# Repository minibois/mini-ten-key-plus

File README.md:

# mini-ten-key-plus
## Repository for the mini Ten Key Plus, a Pro Micro based numpad/macropad PCB, suitable for up to 25 MX(-like) keyswitches and a (tactile) rotary encoder.
It is recommended to download the latest release of this project: https://github.com/minibois/ten-key-plus/releases

 This PCB can be used using a 3D printed plate and case, also provided in this repository

 _Render of the front and back of the PCB respectively_

 << [License](https://github.com/minibois/ten-key-plus/tree/master/LICENSE) || [Assembly Guide](https://github.com/minibois/ten-key-plus/blob/master/Documents/Assembly%20Guide.pdf) || BOM ([Octoparts](https://octopart.com/bom-tool/pvFPXgm8)) / ([.txt](https://github.com/minibois/ten-key-plus/blob/master/Documents/BOM.txt)) / ([.xlsx](https://github.com/minibois/ten-key-plus/blob/master/Documents/BOM.xlsx)) || [Supported layouts](https://raw.githubusercontent.com/minibois/ten-key-plus/master/Documents/Layouts/layouts.png) || Schematic ([.pdf](https://github.com/minibois/ten-key-plus/blob/master/Documents/Schematic.pdf)) / ([.sch](https://github.com/minibois/ten-key-plus/blob/master/mini-ten-key-plus.sch)) || PCB ([.pdf](https://github.com/minibois/ten-key-plus/blob/master/Documents/PCB.pdf)) / ([.kicad_pcb](https://github.com/minibois/ten-key-plus/blob/master/mini-ten-key-plus.kicad_pcb)) >>

 The PCB and schematic are licensed under CERN-OHL-S v2, full license details can be found here: https://github.com/minibois/ten-key-plus/tree/master/LICENSE/LICENSE.txt.

## Libraries used in this project (most of them adapted to this project):
 * That-Canadian's KiCad_labs (for the D-SOD123_axial-dual): https://github.com/That-Canadian/KiCad_Libs
 * Type-C.Pretty: https://github.com/ai03-2725/Type-C.pretty
 * MX_Alps_Hybrid: https://github.com/ai03-2725/MX_Alps_Hybrid
 * random-keyboard-parts (for a reset switch): https://github.com/ai03-2725/random-keyboard-parts.pretty

### This PCB file and schematic is provided - as per CERN-OHL-S v2 section 6 - _without any warranty_ (implied or otherwise). https://ohwr.org/cern_ohl_s_v2.pdf
### The assembly guide is provided under the CC BY-SA 4.0, without any warranty (implied or otherwise): https://creativecommons.org/licenses/by-sa/4.0/legalcode

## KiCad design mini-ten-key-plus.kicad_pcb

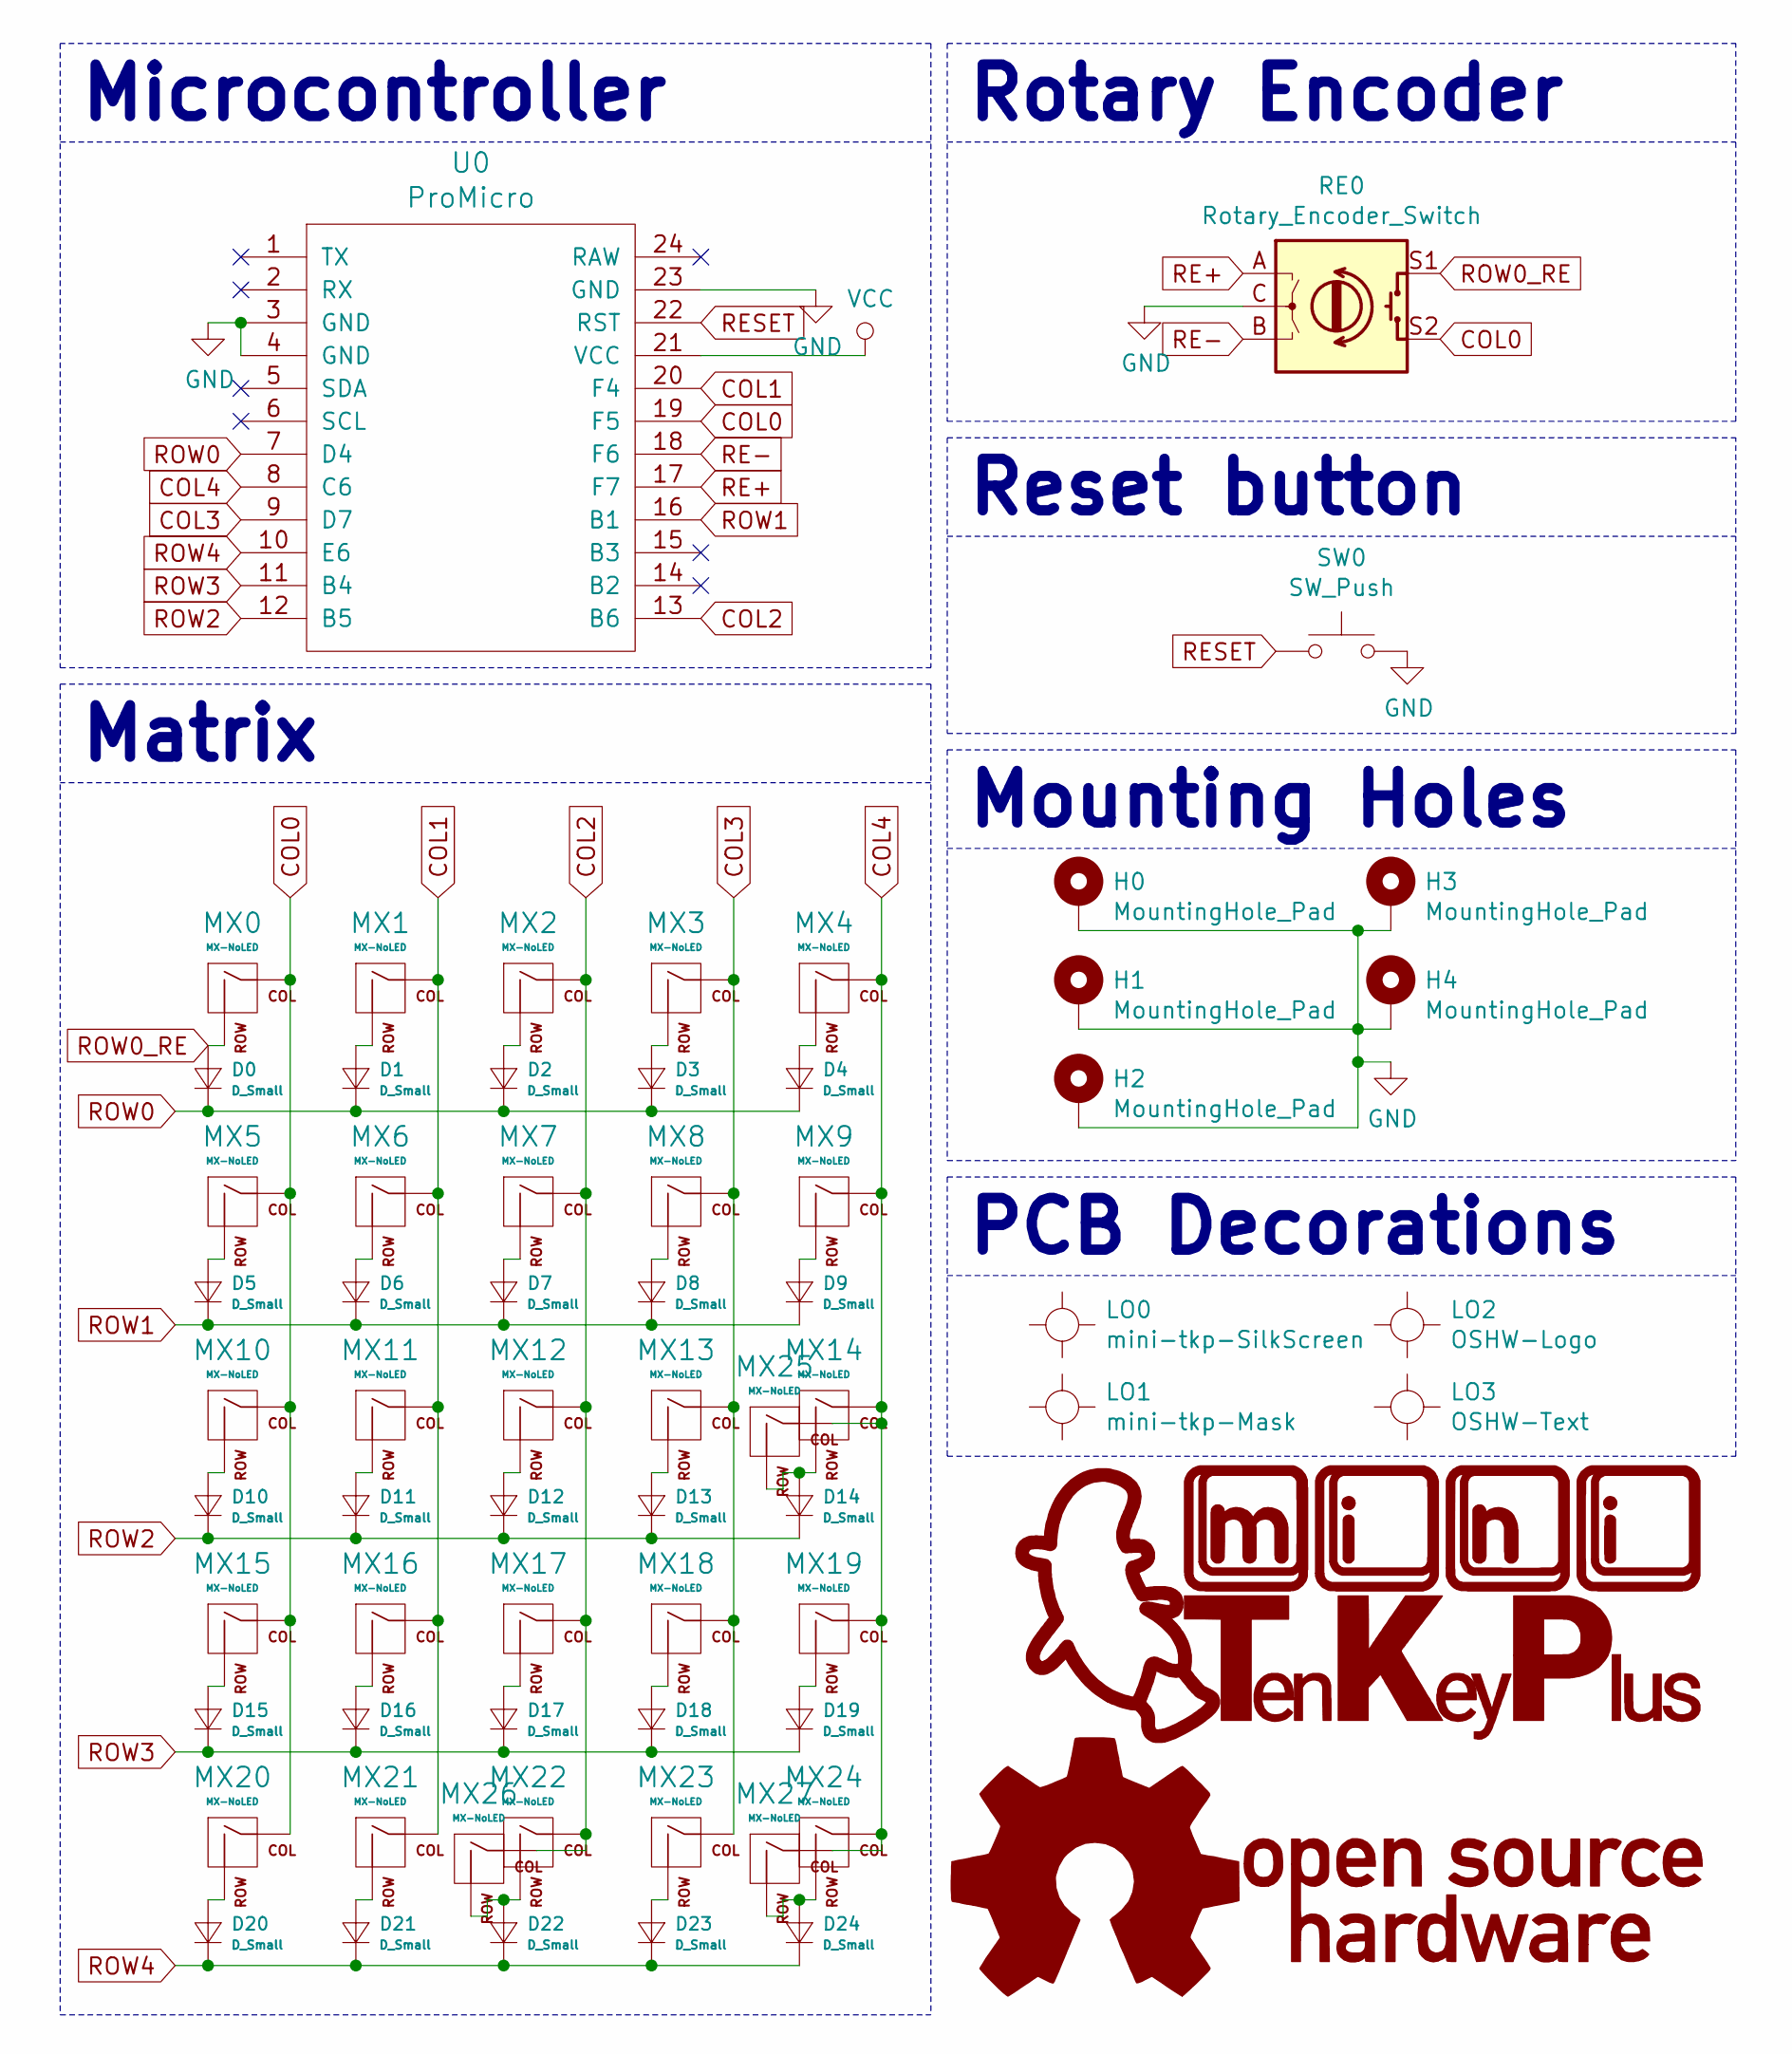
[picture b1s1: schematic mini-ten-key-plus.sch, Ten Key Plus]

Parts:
D0, D1, D2, D3, D4, D5, D6, D7, D8, D9, D10, D11, D12, D13, D14, D15, D16, D17, D18, D19, D20, D21, D22, D23, D24: D_Small; D_SOD123_axial-dual
H0, H1, H2, H3, H4: MountingHole_Pad; MountingHole_2.2mm_M2_Pad_tweaked
LO0: mini-tkp-SilkScreen; mini-TKP-BSilk
LO1: mini-tkp-Mask; mini-TKP-BMask
LO2: OSHW-Logo
LO3: OSHW-Text
MX0, MX1, MX2, MX3, MX4, MX5, MX6, MX7, MX8, MX9, MX10, MX11, MX12, MX13, MX14, MX15, MX16, MX17, MX18, MX19, MX20, MX21, MX22, MX23, MX24: MX-NoLED; MXOnly-1U-NoLED_tweak
MX25, MX27: MX-NoLED; MXOnly-2U-NoLED_tweak
MX26: MX-NoLED; MXOnly-2U-NoLED_FLIPPED_tweak
RE0: Rotary_Encoder_Switch; RotaryEncoder_Alps_EC11E-Switch-Vertical-EDIT
SW0: SW_Push; SKQG-1155865
U0: ProMicro

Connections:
COL0: MX0.1 (COL), MX5.1 (COL), MX10.1 (COL), MX15.1 (COL), MX20.1 (COL), RE0.S2, U0.19 (F5)
COL1: MX1.1 (COL), MX6.1 (COL), MX11.1 (COL), MX16.1 (COL), MX21.1 (COL), U0.20 (F4)
COL2: MX2.1 (COL), MX7.1 (COL), MX12.1 (COL), MX17.1 (COL), MX22.1 (COL), MX26.1 (COL), U0.13 (B6)
COL3: MX3.1 (COL), MX8.1 (COL), MX13.1 (COL), MX18.1 (COL), MX23.1 (COL), U0.9 (D7)
COL4: MX4.1 (COL), MX9.1 (COL), MX14.1 (COL), MX19.1 (COL), MX24.1 (COL), MX25.1 (COL), MX27.1 (COL), U0.8 (C6)
GND: H0.1, H1.1, H2.1, H3.1, H4.1, RE0.C, SW0.2, U0.3 (GND), U0.4 (GND), U0.23 (GND); also elsewhere on the board
unnamed: D1.2 (A), MX1.2 (ROW)
unnamed: D2.2 (A), MX2.2 (ROW)
unnamed: D3.2 (A), MX3.2 (ROW)
unnamed: D4.2 (A), MX4.2 (ROW)
unnamed: D5.2 (A), MX5.2 (ROW)
unnamed: D6.2 (A), MX6.2 (ROW)
unnamed: D7.2 (A), MX7.2 (ROW)
unnamed: D8.2 (A), MX8.2 (ROW)
unnamed: D9.2 (A), MX9.2 (ROW)
unnamed: D10.2 (A), MX10.2 (ROW)
unnamed: D11.2 (A), MX11.2 (ROW)
unnamed: D12.2 (A), MX12.2 (ROW)
unnamed: D13.2 (A), MX13.2 (ROW)
unnamed: D14.2 (A), MX14.2 (ROW), MX25.2 (ROW)
unnamed: D15.2 (A), MX15.2 (ROW)
unnamed: D16.2 (A), MX16.2 (ROW)
unnamed: D17.2 (A), MX17.2 (ROW)
unnamed: D18.2 (A), MX18.2 (ROW)
unnamed: D19.2 (A), MX19.2 (ROW)
unnamed: D20.2 (A), MX20.2 (ROW)
unnamed: D21.2 (A), MX21.2 (ROW)
unnamed: D22.2 (A), MX22.2 (ROW), MX26.2 (ROW)
unnamed: D23.2 (A), MX23.2 (ROW)
unnamed: D24.2 (A), MX24.2 (ROW), MX27.2 (ROW)
RE+: RE0.A, U0.17 (F7)
RE-: RE0.B, U0.18 (F6)
RESET: SW0.1, U0.22 (RST); also elsewhere on the board
ROW0: D0.1 (K), D1.1 (K), D2.1 (K), D3.1 (K), D4.1 (K), U0.7 (D4)
ROW0_RE: D0.2 (A), MX0.2 (ROW), RE0.S1
ROW1: D5.1 (K), D6.1 (K), D7.1 (K), D8.1 (K), D9.1 (K), U0.16 (B1)
ROW2: D10.1 (K), D11.1 (K), D12.1 (K), D13.1 (K), D14.1 (K), U0.12 (B5)
ROW3: D15.1 (K), D16.1 (K), D17.1 (K), D18.1 (K), D19.1 (K), U0.11 (B4)
ROW4: D20.1 (K), D21.1 (K), D22.1 (K), D23.1 (K), D24.1 (K), U0.10 (E6)
VCC: U0.21 (VCC)

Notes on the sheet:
Matrix
Microcontroller
Reset button
Mounting Holes
PCB Decorations
Rotary Encoder

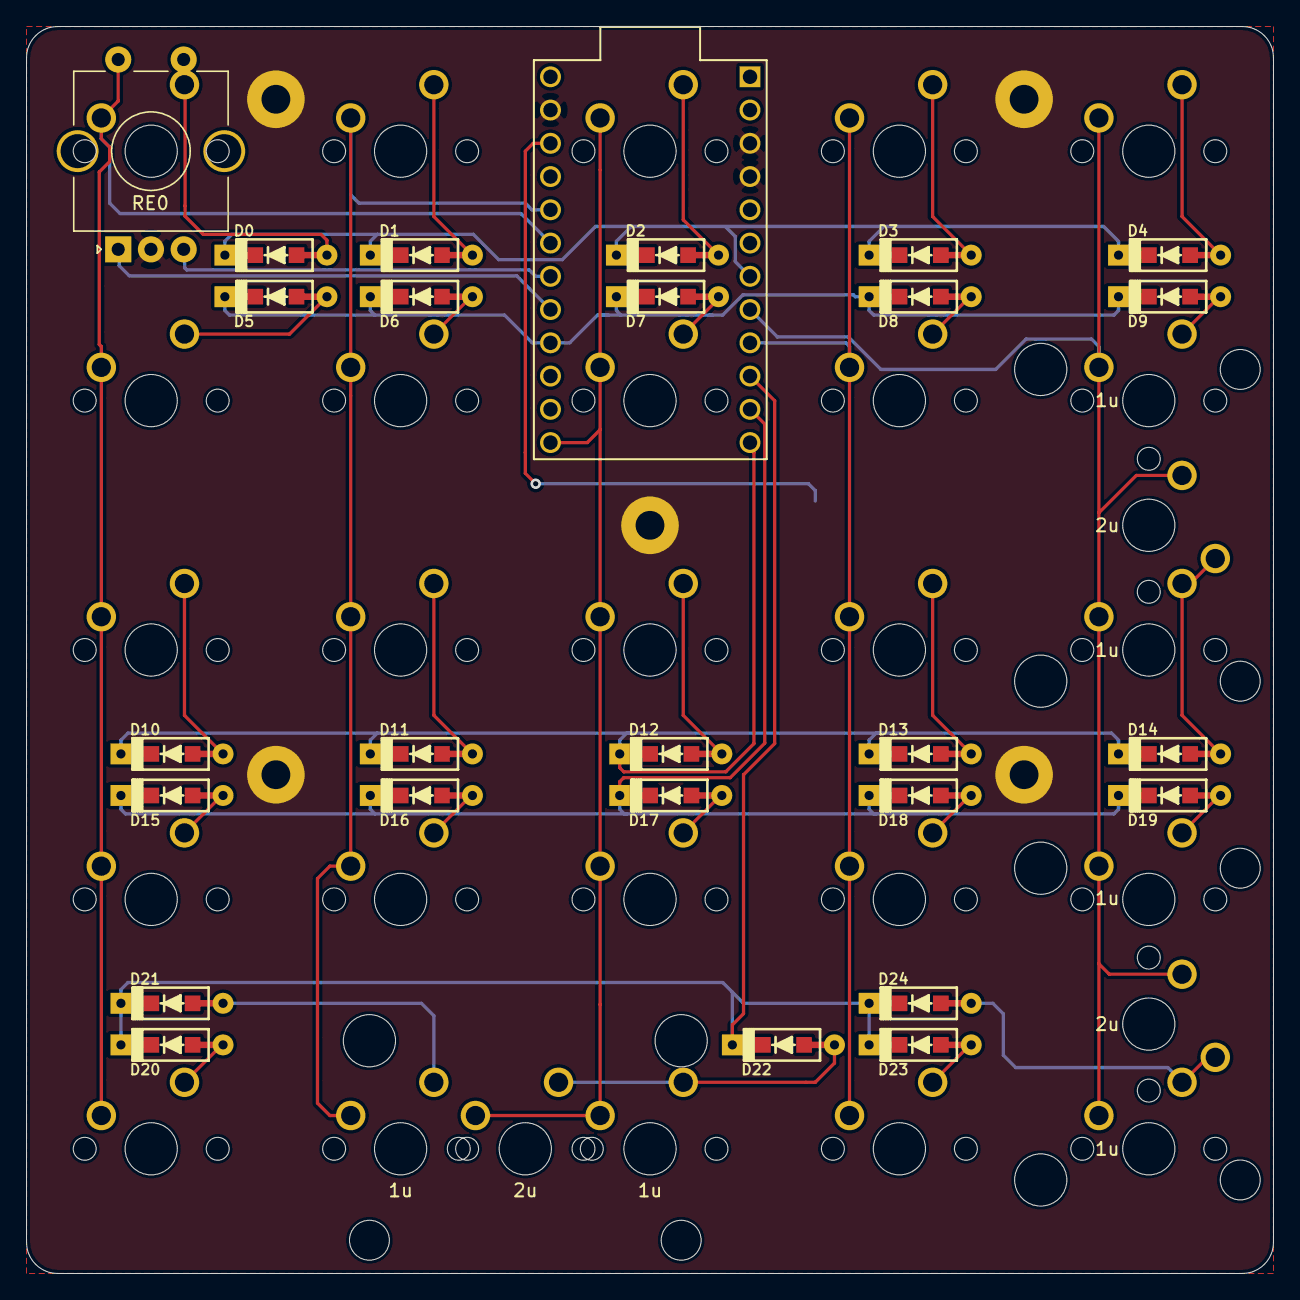
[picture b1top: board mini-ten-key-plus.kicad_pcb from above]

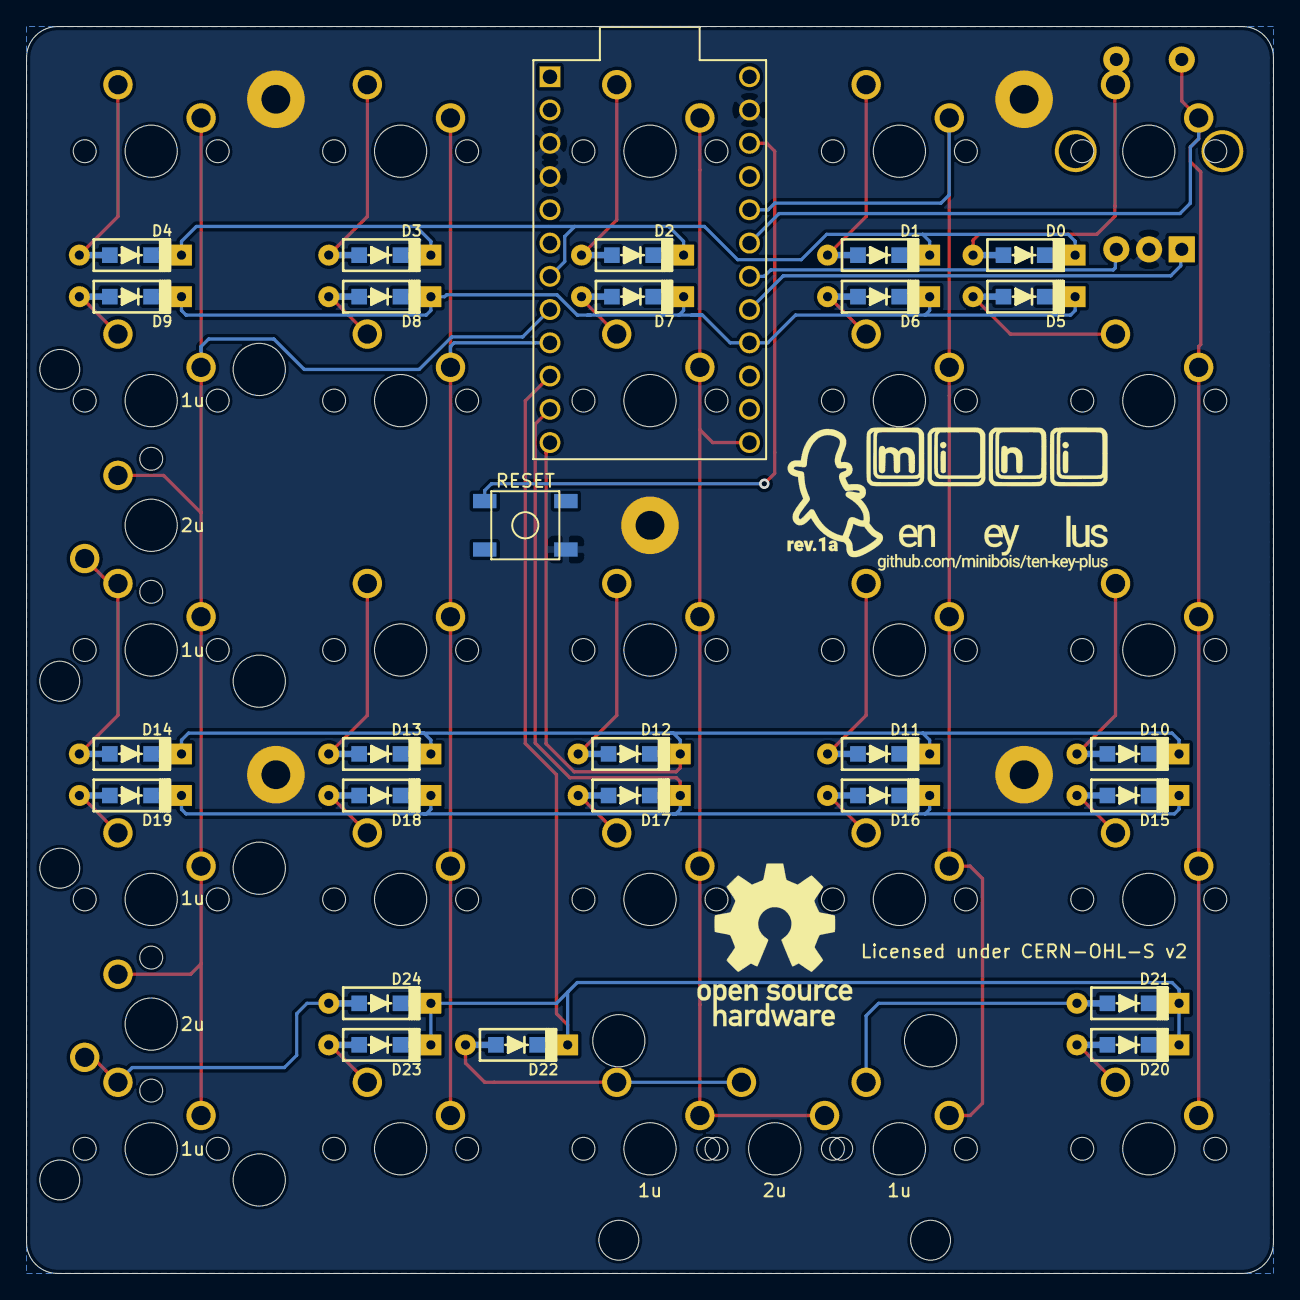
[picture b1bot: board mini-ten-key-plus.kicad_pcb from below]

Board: 2 copper layers, 95.2 x 95.2 mm, 65 parts (3 on the bottom side), 39 nets.

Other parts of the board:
RESET: SW_Push; SKQG-1155865

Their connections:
GND: RESET.2; also elsewhere on the board
RESET: RESET.1; also elsewhere on the board

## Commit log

2021-10-20 Created project.
2021-10-20 Added submodules via Git
2021-10-20 Added libraries via KiCAD
2021-10-20 Added Pro Micro library
2021-10-20 Added Pro Micro library to KiCAD
2021-10-20 Added MX library, for the symbol library
2021-10-20 Update symbol library
2021-10-20 Added random keyboard parts, for reset switch
2021-10-21 Laid out PCB, ran most traces (sans col/row to MCU)
2021-10-22 Did practice col/row wiring
2021-10-22 Ran first versions of row/col pins
2021-10-22 Rotated Pro Micro around
2021-10-22 Flipped Pro Micro and redid rows/cols
2021-10-24 Trying to remove row 4 trace
2021-10-28 General routing
2021-10-29 Added extra column of keys on the left side
2021-11-01 Cleaned up schematic
2021-11-02 Added rotary encoder
2021-11-10 Added TKP logo, restructured schematic
2021-11-10 Made gerber files
2021-12-17 Added layout image and general edits
2021-12-20 Added BOM.txt and BOM.xlsx
2021-12-20 Updated BOM.txt
2021-12-21 Added LICENSE
2021-12-21 Added additional info to PCB/Schematic and added PCB/Schematic PDF
2022-01-02 Added case, plate, images and updated README.md
2022-01-02 Edited README.md full build image link

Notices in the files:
mini-ten-key-plus.kicad_pcb:
Full License: https://github.com/minibois/ten-key-plus/tree/master/LICENSE
This PCB file describes Open Hardware and is licensed under the CERN-OHL-S v2.
mini-ten-key-plus.sch:
This schematic describes Open Hardware and is licensed under the CERN-OHL-S v2.
